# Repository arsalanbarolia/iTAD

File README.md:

# Intelligent Telepresence Assistive Device (iTAD)

> Intelligent Telepresence Assistive Device (iTAD) in a netural state.

> A more detailed and thorough walk-through of the wiring and PCB production process can be found in [Final Report](files/FinalReport.pdf).
---

### Table of Contents

- [Description](#description)
- [Features](#features)
- [My Contribution](#my-contribution)
- [Team Contribution](#team-contribution)
- [Author Info](#author-info)

---

## Description

<h3><u>What are telepresence devices?</u></h3>
<p style='text-align: justify'>Telepresence devices use robotic platforms equipped with sensors and communication tools to execute tasks remotely. Commercially-available models typically offer limited mobility and interaction capabilities. Many lack a means of allowing the user to physically interact with the remote environment and are not designed to be accessible by people with disabilities, barring them from effectively using this up-coming technology.
</p>

<h3><u>What is iTAD?</u></h3>
<p style='text-align: justify'>Intelligent Telepresence Assistive Device (iTAD) is a robotic platform which facilitates real-time communications and remote interactions in a variety of application areas. iTAD aims to address technological barriers which can prevent people with disabilities from accessing the healthcare they need or communicating/interacting with loved ones in independent living centres. iTAD can make healthcare more accessible by connecting remote medical professionals and patients, including those that are permanently or temporarily disabled, as well as assist nurses, other doctors and family members. In independent living facilities, iTAD can aid the elderly with different tasks such as walking, eating, administering medications, and remotely communicating with healthcare professionals. iTAD’s robust design and versatility offers a cost-effective solution for addressing a variety of scenarios that help connect individuals and facilitate interactions. In addition, iTAD is designed to safely fit within dynamic hospitals and independent living facilities, requiring no changes to be made to existing infrastructures.
</p>

[Back To The Top](#project)

---

## Features

<h3><u>The Head</u></h3>

<p style='text-align: justify'>The head is compromised of the tablet, camera, and LiDAR (Light Detection and Ranging) sensor. An end-user is able to engage in natural-feeling interactions thanks to the centralized head structure making it possible to look at the tablet while looking into the camera. The tablet streams the live audiovisual stream from the desktop application. Facial detection software is used to detect the largest face in a frame, allowing the camera to follow it by using the camera’s pan and tilt functions, preventing the remote user from needing to constantly readjust the camera during a conversation. The camera’s pan and tilt functions and the removable tablet allow people at different heights to accessibly communicate through iTAD. In addition, the head is able to rotate via the neck structure, allowing users to easily address someone not directly in front of iTAD. The LiDAR sensor enables iTAD to map its surrounding area for autonomous navigation.</p>

<h3><u>The Arm</u></h3>

<p style='text-align: justify'>
The communication experience is further enhanced with the use of a <b><u>5 degree-of-freedom (dof) arm</u></b>, allowing the user to physically interact with a large area within its surroundings. The position of the end-effector, or gripper, can be intuitively controlled by toggling between arm and drivetrain control on the main controller. The versatile <b><u>gripper</u></b> design allows effective grasping of objects with different dimensions and surface finishes. The gripper is instrumented with force sensors and proximity infrared sensors to safely grasp objects and push items. Also, the gripper can be equipped with diagnostic tools, such as a heart rate sensor, to assist remote doctors with patient check-ups.

The <b><u>arm</u></b> can assist people with disabilities by performing various tasks; examples include:

- Lifting light objects
- Moving IV poles
- Flicking light switches
- Pushing elevator buttons (also essential for autonomous navigation capabilities)
</p>

<h3><u>Additional Features</u></h3>
<h4> Communication Platform</h4>
<p style='text-align: justify'>

The highly configurable nature of iTAD’s communication platform allows for the addition of features to ensure that iTAD is compliant with accessibility standards; these include:

- Voice commands for the main functions of the robot, such as start-up and autonomous navigation.
- Filters to assist the visually impaired and individuals who lip-read to view video feeds.
- Real-time subtitles via voice-to-text converters and text-to-voice converters to allow effective communication with deaf or hard-hearing individuals.

<h4> Autonomous Navigation</h4>

To navigate autonomously, a LiDAR (Light Detection and Ranging) sensor maps iTAD’s surroundings, identifying where it is and calculating a path to get to its destination autonomously, by referencing a larger map of the environment.

The video shown demonstrates iTAD’s current mapping abilities. As iTAD, denoted by the right-angle-connected red and green lines, moves throughout a house, it maps the house’s barriers, shown as the black lines, as well as iTAD’s trajectory, shown as the bright green line. Path planning algorithms are then applied to plan a path from iTAD’s current location to a desired location chosen by a user on the map.

</p>

https://user-images.githubusercontent.com/35279249/184552282-5e54822b-e0f5-4f1f-b2eb-ef36244b4058.mp4

[Back To The Top](#project)

---

## My Contribution

> > Please note that a more detailed and thorough walk-through of the wiring and PCB production process can be found in [Final Report](files/FinalReport.pdf). This section will just give a brief overview of some of the actions taken to acheive a successful wiring and functioning layout.

<h3><u>Purpose</u></h3>
<p style='text-align: justify; text-indent: 1cm'>
One of the focus for this years team was to improve the wiring organization and
overall appearance of the iTAD robot. To accomplish this goal, majority of the
wires can be implemented on a PCB board to remove the visible wires as well
as uphold its functionality. Currently, the wiring state of the robot is a disaster
and needs to be organized. For a better insight, majority of the wires are tangled
with one another and is hard to see where certain wires are connected as some
do change colour mid-way. Some wires can also be easily disconnected when a
small external force is applied to the wire.
</p>
<p style='text-align: justify; text-indent: 1cm'>
The following sections will explore how the schematic and board layout was devel-
oped using EAGLE and diffrent techniques used to ensure a fast and responsive
PCB for the PWM and the Odroid section of iTAD.
</p>

<p style='text-align: justify; text-indent: 1cm'>
There was no prior schematic given to us for the existing robot so I had to design and verfiy both the communication and motor schematic. The image below showcases the two schematics that were genereated using CircuitMaker.
</p>

<table>
  <tr align='center'>
    <td>Communication Schematic</td>
     <td>Power Schematic</td>
  </tr>
  <tr>
    <td></td>
    <td></td>
  </tr>
 </table>

<h3><u>Summary</u></h3>

<p style='text-align: justify; text-indent: 1cm'>
First off, a visionary
overview that shows how a PCB will be used to better the wire
organization of the robot. It can be seen below in Figure 1.
</p>

<p align='center'> Figure 1: Visual integration of visible wires between the Odroid and PWM</p>
<p style='text-align'>
From this vision, a schematic was created along with a table of components,
Figure 2 and Table 1, respectively.
</p>

<figure align='center'>
 
</figure>
<p align='center'>Figure 2: Schematic of PCB for Odroid and PWM wire management</p>

<p align='center'>Table 1: List of components that will be mounted on the PCB</p>
<figure align='center'>
 
</figure>

<p style='text-align: justify; text-indent: 1cm'>
The future goals mentioned in tech memo 1 mentioned finalizing the list of
components and inserting the terminal block in the schematic which was substi-
tuted with a 40-pin female header. Once these would be completed, Professor
Qadi would review the design and components and proceed with the manufac-
turing and construction of the PCB.
</p>

<p style='text-align: justify; text-indent: 1cm'>
After self learning EAGLE and the use of various important libraries, I was able to create a final gerber file that showcased how the internal wiring of the PCB would look. Figure 3 shows the gerber file below.
</p>

> The gerber files for all layers of the PCB can be found under the [Gerber File](/files/CAMOutputs/GerberFiles/) folder.

<figure align='center'>
 
</figure>

<p align='center'>Figure 3: Finalized board layout along with its physical connections</p>

<p style='text-align: justify; text-indent: 1cm'>
Labels and text were also added using the text function on EAGLE that
could be seen on the silkscreen layer. This writing helps indicate the person
using the PCB where all the pin numbers are to avoid any errors in the wiring.
Please note that the red wire in Figure 3 was routed on the top layer of the cop-
per whereas the blue indicates the connections at the bottom layer. This helps
organize the different wires without having too many wires on one layer. Once
the board was produced, the ERC (Electrical Rule Check) and DRC (Design
Rule Check) was used to check that no additional or unnecessary wires were
connected on the schematic and the board, respectively. No errors were found.
Thus, the board was ready to be manufactured and sent to PCBway. Figure 4 displays the specs that were selected help manufacture the PCB based on the Gerber files sent.
</p>

<figure align='center'>
 
</figure>
<p align='center'>Figure 4: Product detail of the PCB sent to PCBway based on the Gerber Files</p>

<p style='text-align: justify; text-indent: 1cm'>
These specifications were chosen and selected based on the Gerber files sent.
Gerber files help manufactures know exactly what is on every layer of your PCB
and the specifications you set during the design process. Figure 5, below, depicts
an example of the Gerber file for my board layout.
</p>

<figure align='center'>

</figure>
<p align='center'>Figure 5: My PCB Gerber file using an online Gerber viewer</p>

<p style='text-align: justify; text-indent: 1cm'>
This Gerber file was viewed using an online Gerber viewer. It is very impor-
tant to view your Gerber file using an online viewer or another software as some
compiling issues do occur. This allows the designer of the PCB to verify that
the connections on the PCB are correctly routed and that the manufacturer
knows how the PCB needs to be produced.
<p>
<p style='text-align: justify; text-indent: 1cm'>
Once this order was processed, the PCB was shipped and delivered along
with its components, in 1 week and 2 days, respectively. In the figure below,
Figure 6, an image of the PCB manufactured is shown.
</p>

<figure align='center'>
 
</figure>
 <p align='center'>Figure 6: Manufactured PCB from PCBway</p>

[Back To The Top](#project)

---

## Team Contribution

<h4>Class of 2020 MAAE 4907 at Carleton University</h4>
- Team of 25 students

[Back To The Top](#project)

---

## Author Info

<h4> Arsalan Barolia</h4>

- LinkedIn - [linkedin.com/in/arsalanbarolia](https://www.linkedin.com/in/arsalanbarolia)
- GitHub - [github.com/arsalanbarolia](https://github.com/arsalanbarolia)
- Website - [arsalanbarolia.com](https://arsalanbarolia.com)

[Back To The Top](#project)

---

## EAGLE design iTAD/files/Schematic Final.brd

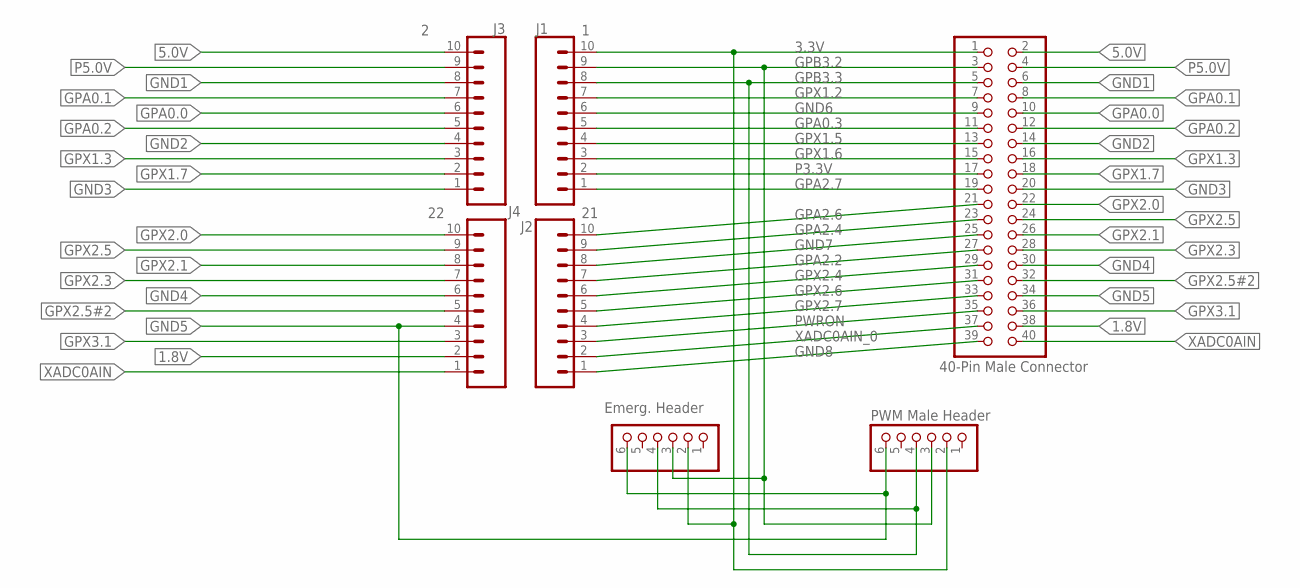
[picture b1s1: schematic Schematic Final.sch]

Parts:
J1: 1; 1X10
J2: 21; 1X10
J3: 2; 1X10
J4: 22; 1X10
JP1: 40-Pin Male Connector; 2X20
JP2: Emerg. Header; 1X06
JP4: PWM Male Header; 1X06

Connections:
1.8V: J4.2, JP1.38
3.3V: J1.10, JP1.1, JP2.2, JP4.2
5.0V: J3.10, JP1.2
GND1: J3.8, JP1.6
GND2: J3.4, JP1.14
GND3: J3.1, JP1.20
GND4: J4.6, JP1.30
GND5: J4.4, JP1.34, JP2.6, JP4.6
GND6: J1.6, JP1.9
GND7: J2.8, JP1.25
GND8: J2.1, JP1.39
GPA0.0: J3.6, JP1.10
GPA0.1: J3.7, JP1.8
GPA0.2: J3.5, JP1.12
GPA0.3: J1.5, JP1.11
GPA2.2: J2.7, JP1.27
GPA2.4: J2.9, JP1.23
GPA2.6: J2.10, JP1.21
GPA2.7: J1.1, JP1.19
GPB3.2: J1.9, JP1.3, JP2.3, JP4.3
GPB3.3: J1.8, JP1.5, JP2.4, JP4.4
GPX1.2: J1.7, JP1.7
GPX1.3: J3.3, JP1.16
GPX1.5: J1.4, JP1.13
GPX1.6: J1.3, JP1.15
GPX1.7: J3.2, JP1.18
GPX2.0: J4.10, JP1.22
GPX2.1: J4.8, JP1.26
GPX2.3: J4.7, JP1.28
GPX2.4: J2.6, JP1.29
GPX2.5: J4.9, JP1.24
GPX2.5#2: J4.5, JP1.32
GPX2.6: J2.5, JP1.31
GPX2.7: J2.4, JP1.33
GPX3.1: J4.3, JP1.36
P3.3V: J1.2, JP1.17
P5.0V: J3.9, JP1.4
PWRON: J2.3, JP1.35
XADC0AIN: J4.1, JP1.40
XADC0AIN_0: J2.2, JP1.37

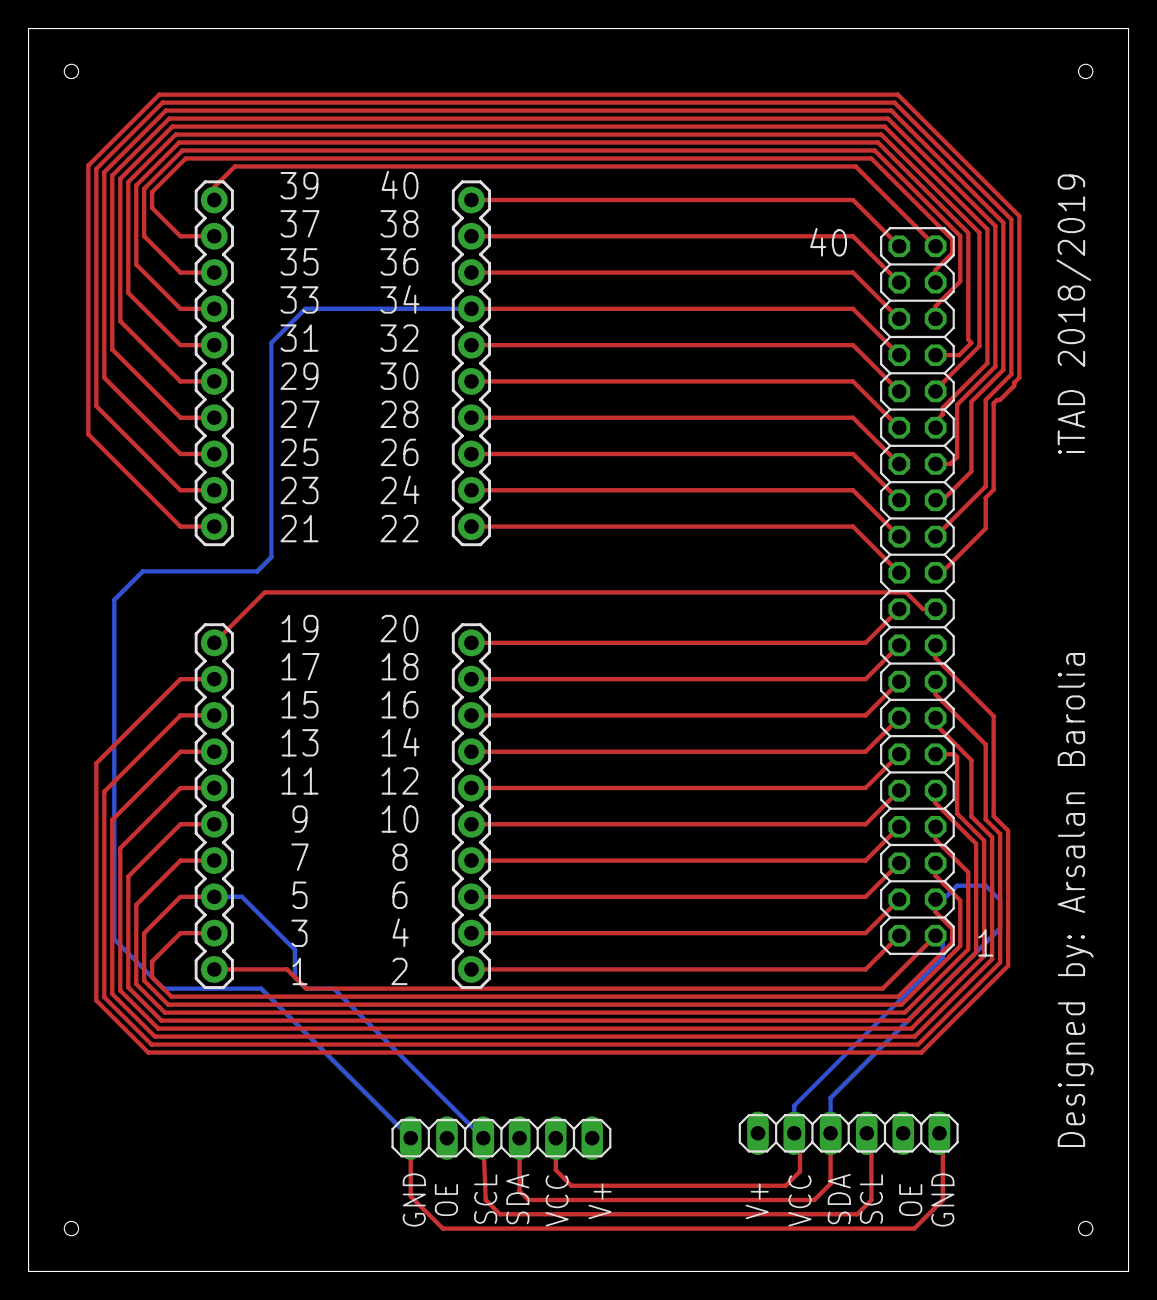
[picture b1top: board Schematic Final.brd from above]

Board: 2 copper layers, 77.0 x 87.0 mm, 7 parts (0 on the bottom side), 40 nets.

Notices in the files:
parts and their libraries:
SparkFun-Connectors: Licensing: Creative Commons ShareAlike 4.0 International - https://creativecommons.org/licenses/by-sa/4.0
